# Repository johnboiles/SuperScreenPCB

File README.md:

View this project on [CADLAB.io](https://cadlab.io/project/1252). 

# SuperScreenPCB

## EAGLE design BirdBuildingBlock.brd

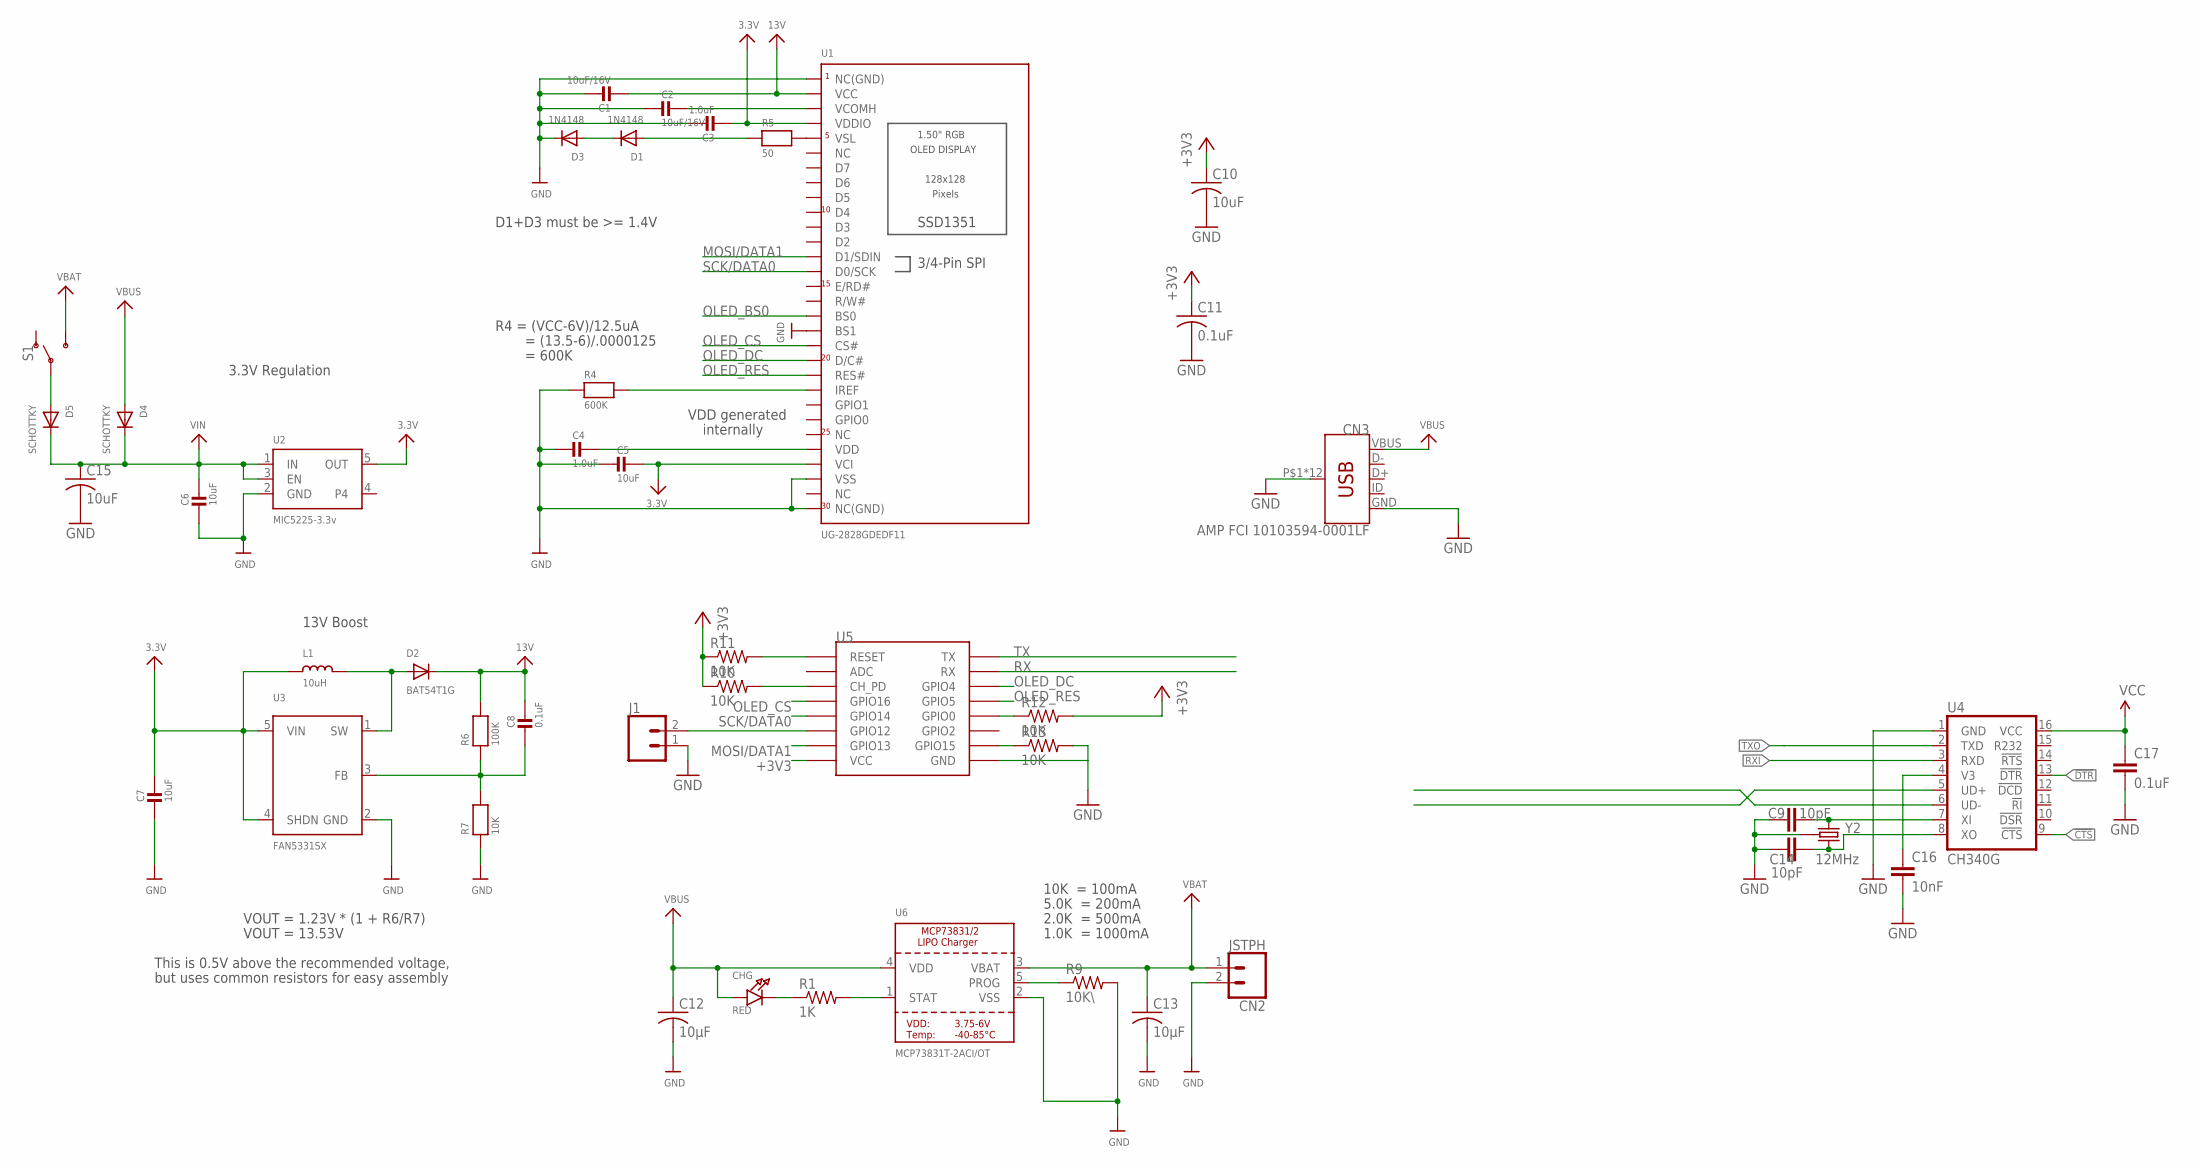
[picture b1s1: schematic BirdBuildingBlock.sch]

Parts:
C1, C2: 10uF/16V; 0805
C3, C4: 1.0uF; 0805
C5, C6, C7: 10uF; 0805
C8: 0.1uF; 0805
C9, C14: 10pF; 0603-CAP
C10, C15: 10uF; C0805
C11: 0.1uF; C0805
C12, C13: 10µF; C0805
C16: 10nF; 0603-CAP
C17: 0.1uF; 0603-CAP
CHG: RED; CHIPLED_0805_NOOUTLINE
CN2: JSTPH; 1X02
CN3: AMP FCI 10103594-0001LF; USB-MICROB-PTH
D1, D3: 1N4148; SOD-323
D2: BAT54T1G; SOD-123
D4, D5: SCHOTTKY; SOD-123FL
J1: CONN_02; 1X02
L1: 10uH; INDUCTOR_1007
R1: 1K; R0805
R4: 600K; 0805
R5: 50; 0805
R6: 100K; 0805
R7: 10K; 0805
R9: 10K\; R0805
R10, R11, R12, R13: 10K; R0805
S1: SWITCH-SPDT-SMD-RIGHT-ANGLE; SWITCH_SPST_SMD_A
U1: UG-2828GDEDF11; FPC_XF2M-3015-1A
U2: MIC5225-3.3v; SOT23-5
U3: FAN5331SX; SOT23-5@1
U4: CH340G; SO016
U5: ESP12SMD; ESP12-SMD
U6: MCP73831T-2ACI/OT; SOT23-5
Y2: 12MHz; CRYSTAL-SMD-3.2X2.5

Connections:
3.3V: C3.2, C5.1, C7.1, L1.P$1 (1), U1.P$4 (VCI), U1.P$27 (VDDIO), U2.5 (OUT), U3.4 (SHDN), U3.5 (VIN)
13V: C1.2, C8.1, D2.C, R6.2, U1.P$29 (VCC)
!CTS: U4.9 (!CTS)
!DTR: U4.13 (!DTR)
+3V3: C10.1, C11.1, R10.1, R11.1, R12.2, U5.VCC
GND: C1.1, C2.2, C3.1, C4.2, C5.2, C6.2, C7.2, C9.1, C10.2, C11.2, C12.2, C13.2, C14.1, C15.2, C16.2, C17.2, CN2.2, CN3.GND, CN3.P$1 (SHIELD), CN3.P$2 (SHIELD), CN3.P$3 (SHIELD), CN3.P$4 (SHIELD), CN3.P$6 (SHIELD), CN3.P$8 (SHIELD), CN3.P$10 (SHIELD), CN3.P$12 (SHIELD), CN3.SHEILD2 (SHIELD), CN3.SHIELD, CN3.SHIELD3 (SHIELD), CN3.SHIELD4 (SHIELD), D3.C, J1.1, R4.1, R7.1, R9.2, R13.2, U1.P$1 (NC(GND)), U1.P$3 (VSS), U1.P$13 (BS1), U1.P$30 (NC(GND)), U2.2 (GND), U3.2 (GND), U4.1 (GND), U5.GND, U6.2 (VSS), Y2.2 (GND), Y2.4 (GND)
IREF: R4.2, U1.P$9 (IREF)
MOSI/DATA1: U1.P$18 (D1/SDIN), U5.GPIO13
unnamed: CHG.C, R1.1
unnamed: R11.2, U5.RESET
unnamed: C4.1, U1.P$5 (VDD)
unnamed: R1.2, U6.1 (STAT)
unnamed: D2.A, L1.P$2 (2), U3.1 (SW)
unnamed: R5.2, U1.P$26 (VSL)
unnamed: D1.A, R5.1
unnamed: C8.2, R6.1, R7.2, U3.3 (FB)
unnamed: R9.1, U6.5 (PROG)
unnamed: C14.2, U4.8 (XO), Y2.3 (2)
unnamed: D1.C, D3.A
unnamed: C9.2, U4.7 (XI), Y2.1
unnamed: R12.1, U5.GPIO0
unnamed: R10.2, U5.CH_PD
unnamed: R13.1, U5.GPIO15
unnamed: J1.2, U5.GPIO12
unnamed: D5.A, S1.2
OLED_BS0: U1.P$14 (BS0)
OLED_CS: U1.P$12 (CS#), U5.GPIO16
OLED_DC: U1.P$11 (D/C#), U5.GPIO4
OLED_RES: U1.P$10 (RES#), U5.GPIO5
RX: U5.RXD0 (RX)
RXI: U4.3 (RXD)
SCK/DATA0: U1.P$17 (D0/SCK), U5.GPIO14
TX: U5.TXD0 (TX)
TXO: U4.2 (TXD)
V3: C16.1, U4.4 (V3)
VBAT: C13.1, CN2.1, S1.3 (S), U6.3 (VBAT)
VBUS: C12.1, CHG.A, CN3.VBUS, D4.A, U6.4 (VDD)
VCC: C17.1, U4.16 (VCC)
VCOMH: C2.1, U1.P$28 (VCOMH)
VIN: C6.1, C15.1, D4.C, D5.C, U2.1 (IN), U2.3 (EN)

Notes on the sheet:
3.3V Regulation
VOUT = 1.23V * (1 + R6/R7)
VOUT = 13.53V
This is 0.5V above the recommended voltage,
but uses common resistors for easy assembly
13V Boost
R4 = (VCC-6V)/12.5uA
= (13.5-6)/.0000125
= 600K
D1+D3 must be >= 1.4V
VDD generated
internally
10K = 100mA
5.0K = 200mA
2.0K = 500mA
1.0K = 1000mA

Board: 2 copper layers, 45 parts (1 on the bottom side), 33 nets, no tracks yet.

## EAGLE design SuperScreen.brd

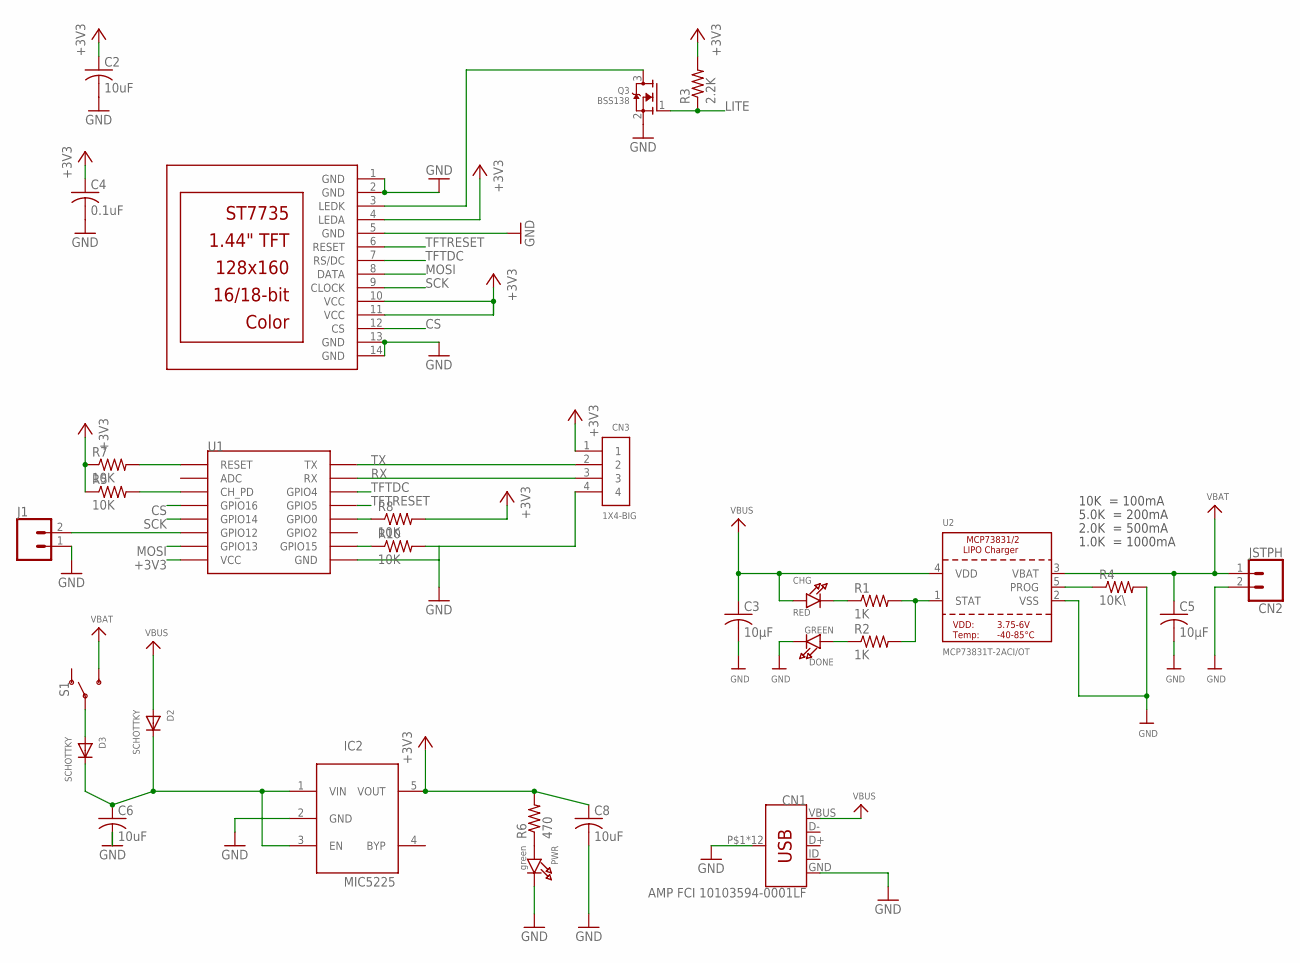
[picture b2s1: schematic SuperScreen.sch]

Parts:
C2, C6, C8: 10uF; C0805
C3, C5: 10µF; C0805
C4: 0.1uF; C0805
CHG: RED; CHIPLED_0805_NOOUTLINE
CN1: AMP FCI 10103594-0001LF; USB-MICROB-PTH
CN2: JSTPH; 1X02
CN3: 1X4-BIG; 1X04-BIG
D2, D3: SCHOTTKY; SOD-123FL
DONE: GREEN; CHIPLED_0805_NOOUTLINE
IC2: MIC5225; SOT23-5L
J1: CONN_02; 1X02
PWR: green; CHIPLED_0805_NOOUTLINE
Q3: BSS138; SOT23-WIDE
R1, R2: 1K; R0805
R3: 2.2K; R0805
R4: 10K\; R0805
R5, R7, R8, R10: 10K; R0805
R6: 470; R0805
S1: SWITCH-SPDT-SMD-RIGHT-ANGLE; SWITCH_SPST_SMD_A
TFT2: DISP_LCD_ST7735_1.44IN; TFT_1.44IN_128_128
U1: ESP12SMD; ESP12-SMD
U2: MCP73831T-2ACI/OT; SOT23-5

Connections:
+3V3: C2.1, C4.1, C8.1, CN3.1, IC2.5 (VOUT), R3.2, R5.1, R6.2, R7.1, R8.2, TFT2.4 (LEDA), TFT2.10 (VCC), TFT2.11 (VCC), U1.VCC
CS: TFT2.12 (CS), U1.GPIO16
GND: C2.2, C3.2, C4.2, C5.2, C6.2, C8.2, CN1.GND, CN1.P$1 (SHIELD), CN1.P$2 (SHIELD), CN1.P$3 (SHIELD), CN1.P$4 (SHIELD), CN1.P$6 (SHIELD), CN1.P$8 (SHIELD), CN1.P$10 (SHIELD), CN1.P$12 (SHIELD), CN1.SHEILD2 (SHIELD), CN1.SHIELD, CN1.SHIELD3 (SHIELD), CN1.SHIELD4 (SHIELD), CN2.2, CN3.4, DONE.C, IC2.2 (GND), J1.1, PWR.C, Q3.2 (S), R4.2, R10.2, TFT2.1 (GND), TFT2.2 (GND), TFT2.5 (GND), TFT2.13 (GND), TFT2.14 (GND), U1.GND, U2.2 (VSS)
LED-: Q3.3 (D), TFT2.3 (LEDK)
LITE: Q3.1 (G), R3.1
MOSI: TFT2.8 (DATA), U1.GPIO13
unnamed: CHG.C, R1.1
unnamed: R7.2, U1.RESET
unnamed: D3.A, S1.2
unnamed: R1.2, R2.2, U2.1 (STAT)
unnamed: J1.2, U1.GPIO12
unnamed: R4.1, U2.5 (PROG)
unnamed: PWR.A, R6.1
unnamed: DONE.A, R2.1
unnamed: R8.1, U1.GPIO0
unnamed: C6.1, D2.C, D3.C, IC2.1 (VIN), IC2.3 (EN)
unnamed: R5.2, U1.CH_PD
unnamed: R10.1, U1.GPIO15
RX: CN3.3, U1.RXD0 (RX)
SCK: TFT2.9 (CLOCK), U1.GPIO14
TFTDC: TFT2.7 (RS/DC), U1.GPIO4
TFTRESET: TFT2.6 (RESET), U1.GPIO5
TX: CN3.2, U1.TXD0 (TX)
VBAT: C5.1, CN2.1, S1.3 (S), U2.3 (VBAT)
VBUS: C3.1, CHG.A, CN1.VBUS, D2.A, U2.4 (VDD)

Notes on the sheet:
10K = 100mA
5.0K = 200mA
2.0K = 500mA
1.0K = 1000mA

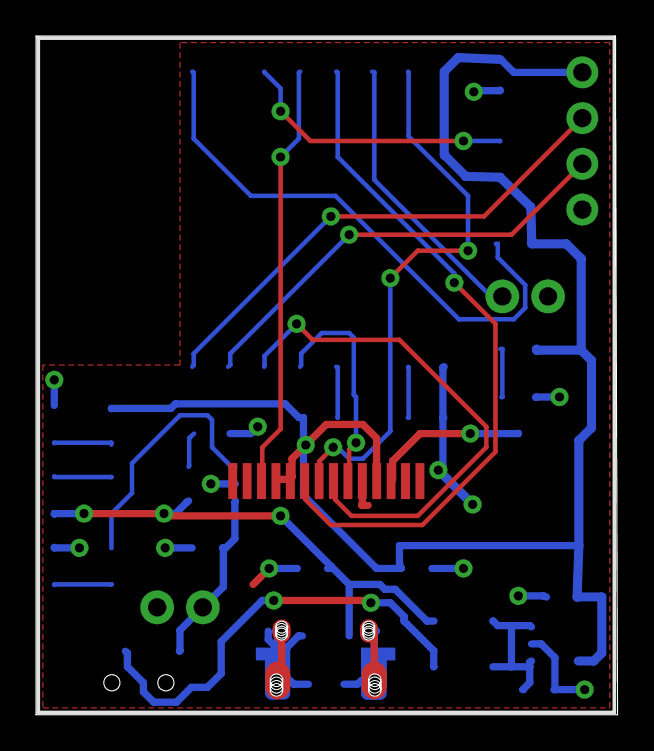
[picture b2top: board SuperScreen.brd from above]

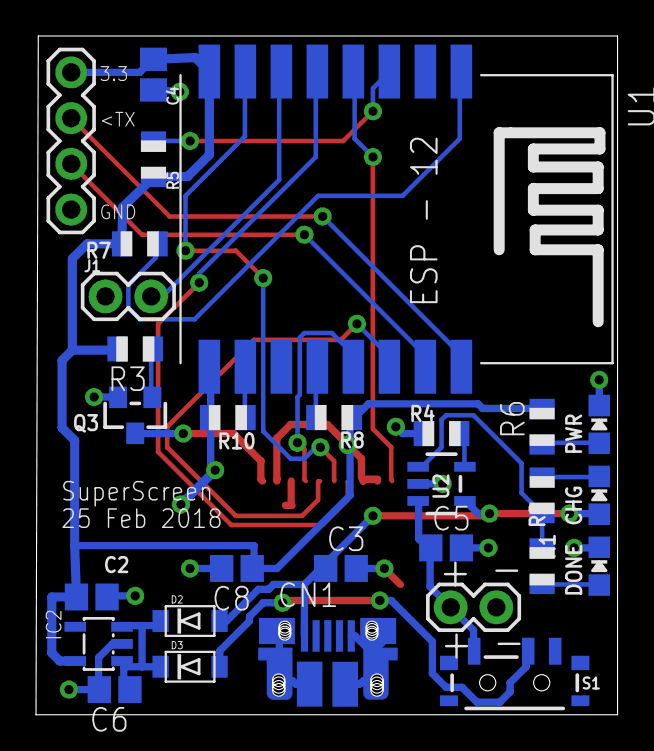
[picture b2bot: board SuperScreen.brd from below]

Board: 2 copper layers, 32.3 x 37.7 mm, 30 parts (29 on the bottom side), 25 nets.

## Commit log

2018-02-24 Initial commit, probably ready to fab board
2018-02-26 Add .job files to .gitignore
2018-02-26 Adding in new usb connector
2018-02-26 Added some gnd vias about to run the autorouter again
2018-02-26 R1 Ordered from OshPark
2018-08-11 Use adafruit's 0805 resistors
2018-08-11 Use Adafruit 0805 caps
2018-08-11 building the first bird building block
2018-08-11 Finalizing some circuit design and cleaning up the pcb layout
2018-08-11 Backlink to CADLAB.io has been added.

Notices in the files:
parts and their libraries:
SparkFun-Connectors: Licensing: Creative Commons ShareAlike 4.0 International - https://creativecommons.org/licenses/by-sa/4.0
SparkFun-Aesthetics: Licensing: CC v3.0 Share-Alike You are welcome to use this library for commercial purposes.
